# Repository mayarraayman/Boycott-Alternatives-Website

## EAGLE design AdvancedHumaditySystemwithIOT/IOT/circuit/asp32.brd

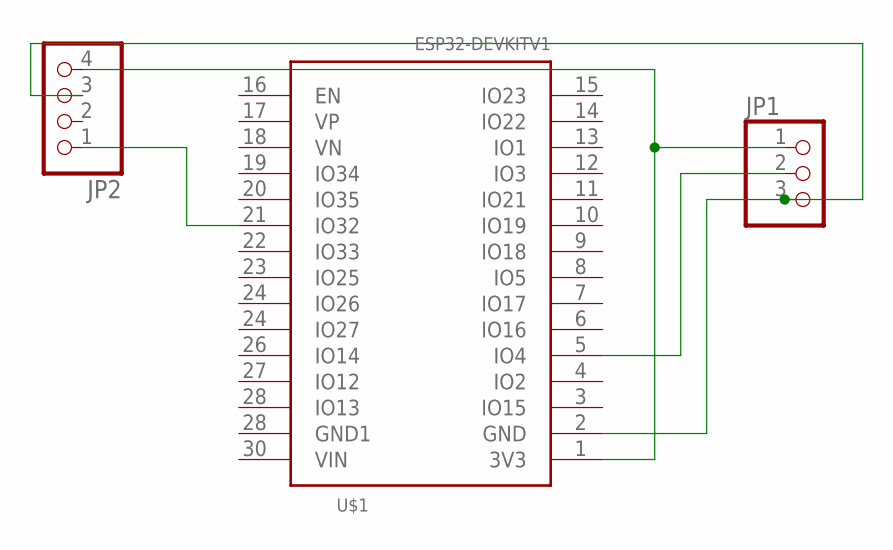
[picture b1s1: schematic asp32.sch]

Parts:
JP1: PINHD-1X3; 1X03
JP2: PINHD-1X4; 1X04
U$1: ESP32DEVKITV1; ESP32-DEVKITV1

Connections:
unnamed: JP1.1, JP2.4, U$1.1 (3V3)
unnamed: JP1.3, JP2.3, U$1.2 (GND)
unnamed: JP1.2, U$1.5 (IO4)
unnamed: JP2.1, U$1.21 (IO32)

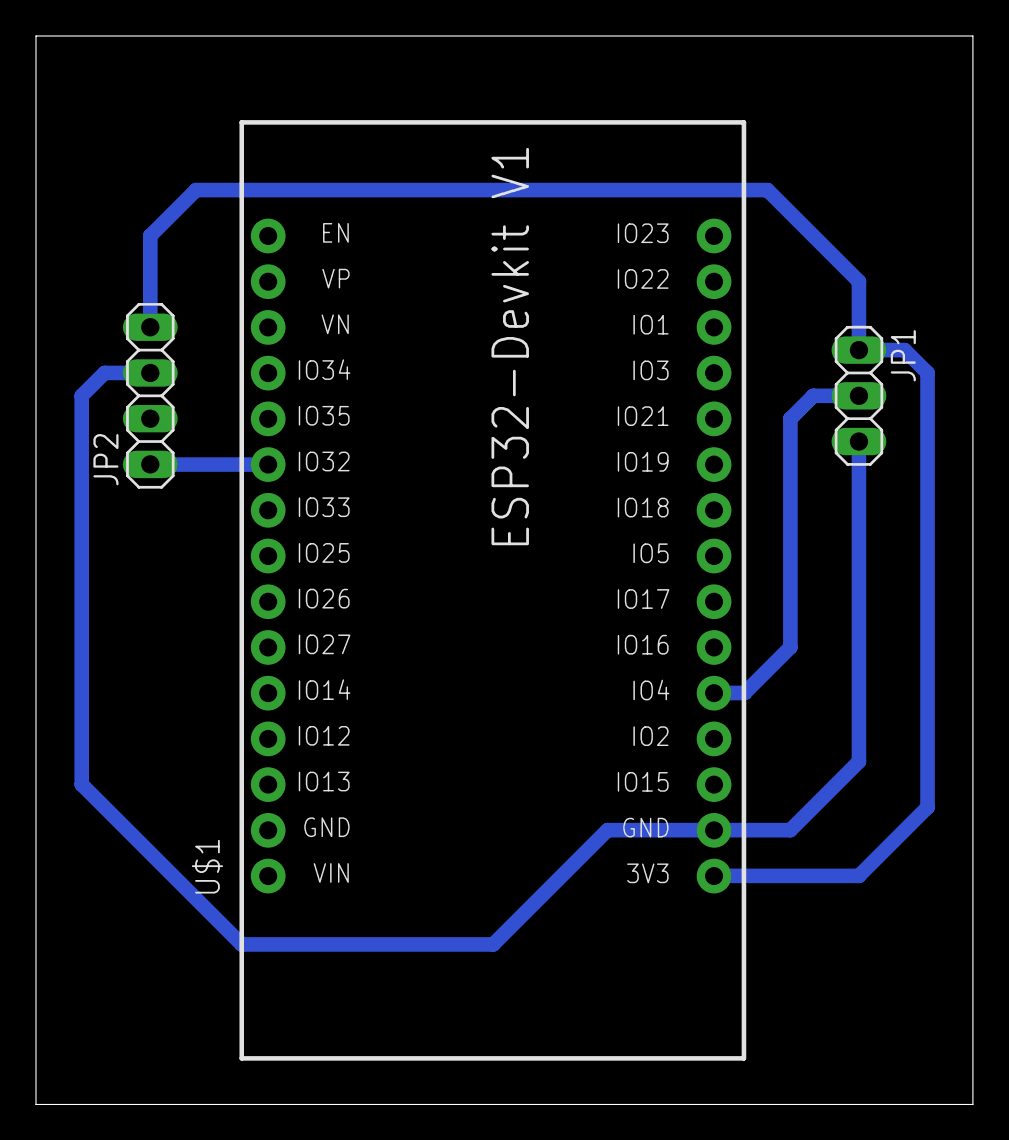
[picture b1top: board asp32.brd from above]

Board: 2 copper layers, 52.1 x 59.4 mm, 3 parts (0 on the bottom side), 4 nets.

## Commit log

2025-04-19 Advanced humidity system using IOT and Arduino
2025-04-19 Boycott Alternatives Searching Website
